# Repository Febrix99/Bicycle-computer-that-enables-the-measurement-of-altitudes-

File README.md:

# Bicycle-computer-that-enables-the-measurement-of-altitudes-
The repository contains files for creating a bicycle counter that also counts elevation gain

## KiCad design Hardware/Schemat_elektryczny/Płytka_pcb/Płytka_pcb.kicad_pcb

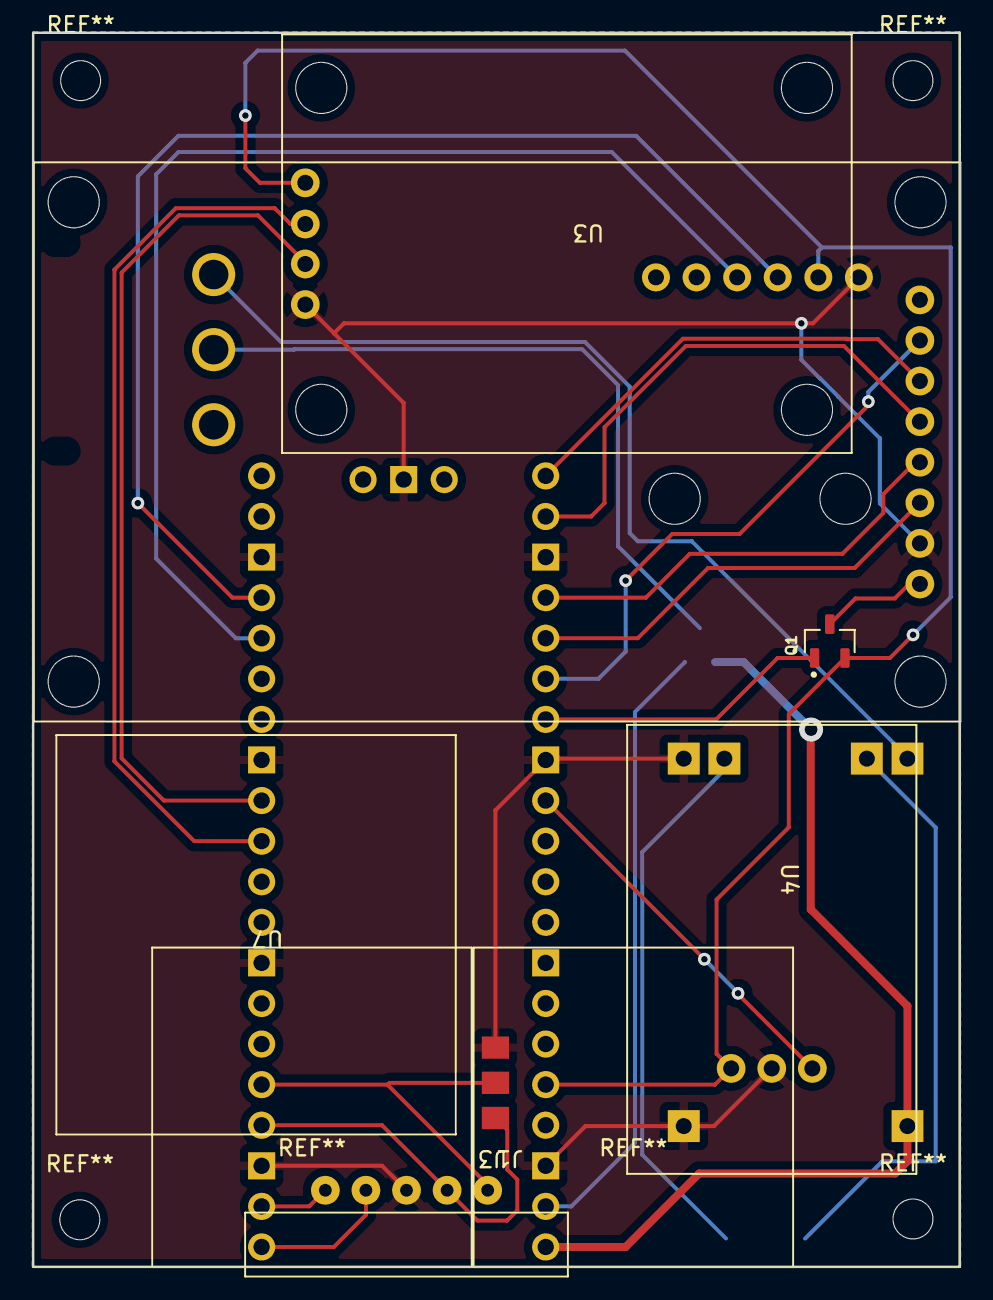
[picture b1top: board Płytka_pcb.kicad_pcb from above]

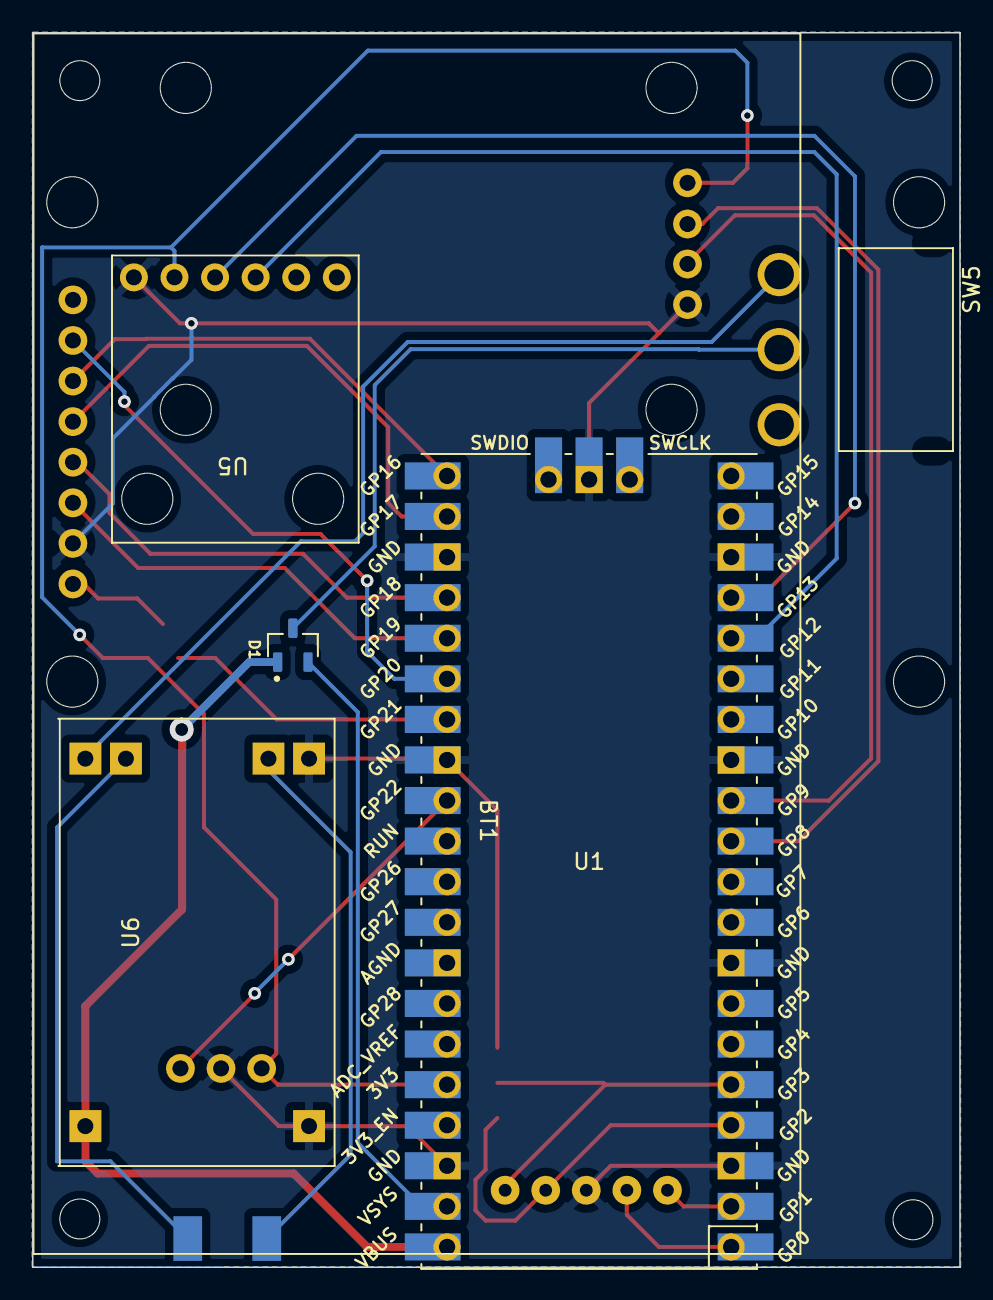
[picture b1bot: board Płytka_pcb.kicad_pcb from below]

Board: 2 copper layers, 58.0 x 77.3 mm, 13 parts (6 on the bottom side), 24 nets.

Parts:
BT1: BL-45A1H 1950 mAh; Battery
D1: DMG2305UX-13; DDTC123TCA-7-F
J1: Connector Femele; 5_pin_90_degree_femele
J3: Buttony_high; 6x6_switch
Q1: MMUN2138LT1G; DDTC123TCA-7-F
SW5: Switch On/Off; Switch_on_off
U1: Pico; RPi_Pico_SMD_TH
U2: 2inch_LCD_IPS; 2_inch_LCD_IPS_FP
U3: GY-GPS6MV2
U4: RobotDyn_1513MA; Buzzer_withouch_gen
U5: SEN-11084; 1513MA_FT
U6: tp4056_C_Module; tp4056_c_module
U7: Antene

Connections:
+3V3: Q1.2 (E), U1.36 (3V3), U3.1 (VCC), U4.3 (VCC), U5.5 (VCC)
+5V: D1.2 (S), U1.39 (VSYS)
+5VP: D1.1 (G), U1.40 (VBUS), U6.1 (VCC)
/Button_1_Pin: J1.5, J3.2, U1.5 (GPIO3)
/Button_2_Pin: J1.4, J3.1, U1.4 (GPIO2)
/Buzzer_Pin: U1.29 (GPIO22), U4.1 (S)
/Cadence_Pin: J1.1, U1.2 (GPIO1)
/I^{2}C1 SCL: U1.17 (GPIO13), U5.4 (SCL)
/I^{2}C1 SDA: U1.16 (GPIO12), U5.3 (SDA)
/SPI1 RST: U1.26 (GPIO20), U2.7 (RST)
/UART1 RX: U1.12 (GPIO9), U3.3 (TX)
/UART1 TX: U1.11 (GPIO8), U3.2 (RX)
/Wheel_Pin: J1.2, U1.1 (GPIO0)
GND: J1.3, J3.3, U1.3 (GND), U1.8 (GND), U1.13 (GND), U1.18 (GND), U1.23 (GND), U1.28 (GND), U1.38 (GND), U1.42 (GND), U2.2 (GND), U3.4 (GND), U4.2 (GND), U5.6 (GND), U6.2 (GND), U6.4 (OUT-)
unnamed: BT1.1 (+), U6.5 (B+)
unnamed: BT1.2 (-), U6.6 (B-)
unnamed: D1.3 (D), SW5.1 (A)
unnamed: Q1.1 (B), U1.27 (GPIO21)
unnamed: Q1.3 (C), U2.1 (VCC)
unnamed: SW5.3 (B), U6.3 (OUT+)
unnamed: U1.21 (GPIO16), U2.6 (DC)
unnamed: U1.22 (GPIO17), U2.5 (CS)
unnamed: U1.24 (GPIO18), U2.4 (CLK)
unnamed: U1.25 (GPIO19), U2.3 (DIN)

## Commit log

2022-10-02 Files
2023-02-25 New file
2023-02-25 Zmiana zmiennej
2023-02-25 Zmiana olejna zmiennej
2023-02-25 98% gotowego softu bez gps
2023-02-25 Create README.md
    The repository contains files for creating a bicycle counter that also counts elevation gain
2023-02-25 Gotowy soft bez parametrow kedencji
2023-02-26 Gotowy soft bez GPS, 2 małe smaczki jeszcze do zdebugowania
2023-02-26 aktalizacja komponetów
2023-02-26 Gotowy w 100% software bez GPS
2023-03-04 Dodanie sterowania pinem wyświetlacza
2023-03-16 Adjustment pinout for pcb
